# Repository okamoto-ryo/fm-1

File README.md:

# fm-1
DIY FM synthesizer

## Overview
<a href="https://okamoto-ryo.github.io/fm-1.html" target="_blank">FM-1</a>

## Requirements
- ARM KEIL uVision 5.0

## やること
- サイン波をsvfで生成するようにする
- ディスプレイのグラフィックを改善
- エンベロープのasymp化
- パラメーター追加
  - LFOの種類

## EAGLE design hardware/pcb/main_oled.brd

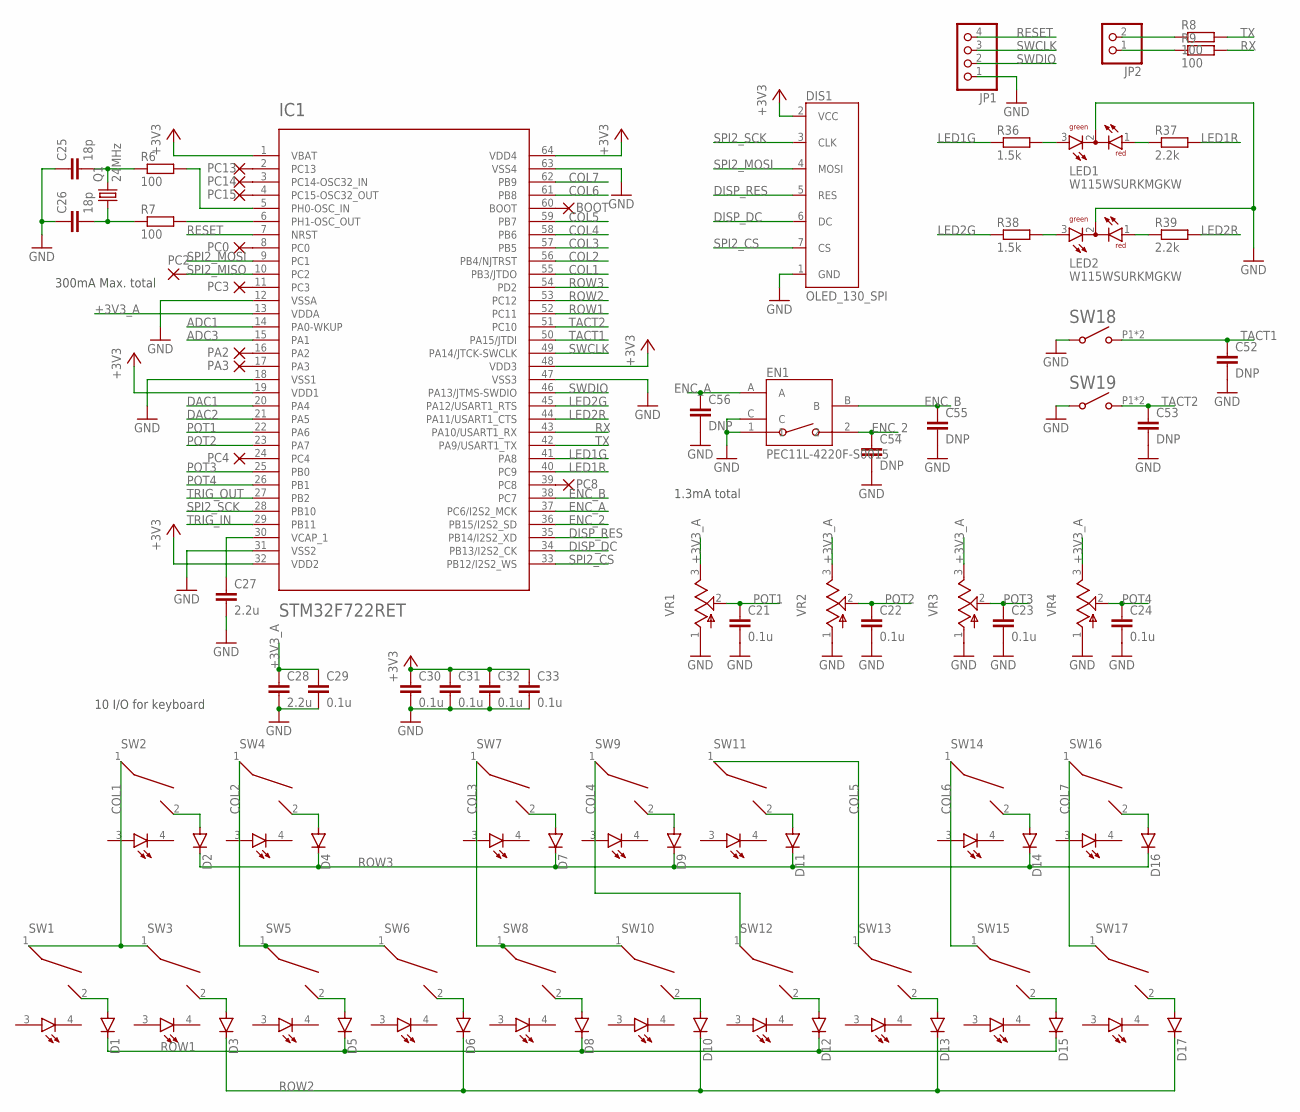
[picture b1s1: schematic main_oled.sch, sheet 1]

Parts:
BOOT: WIREPAD1,6/0,9; 1,6/0,9
C21, C22, C23, C24, C29, C30, C31, C32, C33: 0.1u; C0603
C25, C26: 18p; C0603
C27, C28: 2.2u; C0805
C52, C53, C54, C55, C56: DNP; C0603
D1, D2, D3, D4, D5, D6, D7, D8, D9, D10, D11, D12, D13, D14, D15, D16, D17: DIODE-SOD123; SOD123
DIS1: OLED_130_SPI
EN1: PEC11L-4220F-S0015
IC1: STM32F722RET; TQFP64
JP1: PINHD-1X4; 1X04
JP2: PINHD-1X2; 1X02
LED1, LED2: W115WSURKMGKW
PA2, PA3: WIREPAD1,6/0,9; 1,6/0,9
PC0, PC2, PC3, PC4, PC8, PC13, PC14, PC15: WIREPAD1,6/0,9; 1,6/0,9
Q1: 24MHz; HC49UP
R6, R7, R8, R9: 100; R0603
R36, R38: 1.5k; R0603
R37, R39: 2.2k; R0603
SW1, SW2, SW3, SW4, SW5, SW6, SW7, SW8, SW9, SW10, SW11, SW12, SW13, SW14, SW15, SW16, SW17: CHERRY_MX_LED_WITH_FIXING_PINS; MX1A-XX[R/G/Y]W
SW18, SW19: TACT_TH
VR1, VR2, VR3, VR4: 9MM_V

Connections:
+3V3: C30.1, C31.1, C32.1, C33.1, DIS1.2 (VCC), IC1.1 (VBAT), IC1.19 (VDD1), IC1.32 (VDD2), IC1.48 (VDD3), IC1.64 (VDD4); also elsewhere on the board
+3V3_A: C28.1, C29.1, IC1.13 (VDDA), VR1.3, VR2.3, VR3.3, VR4.3; also elsewhere on the board
ADC1: IC1.14 (PA0-WKUP); also elsewhere on the board
ADC3: IC1.15 (PA1); also elsewhere on the board
COL1: IC1.55 (PB3/JTDO), SW1.1, SW2.1, SW3.1
COL2: IC1.56 (PB4/NJTRST), SW4.1, SW5.1, SW6.1
COL3: IC1.57 (PB5), SW7.1, SW8.1, SW10.1
COL4: IC1.58 (PB6), SW9.1, SW12.1
COL5: IC1.59 (PB7), SW11.1, SW13.1
COL6: IC1.61 (PB8), SW14.1, SW15.1
COL7: IC1.62 (PB9), SW16.1, SW17.1
DAC1: IC1.20 (PA4); also elsewhere on the board
DAC2: IC1.21 (PA5); also elsewhere on the board
DISP_DC: DIS1.6 (DC), IC1.34 (PB13/I2S2_CK)
DISP_RES: DIS1.5 (RES), IC1.35 (PB14/I2S2_XD)
ENC_2: C54.1, EN1.2, IC1.36 (PB15/I2S2_SD)
ENC_A: C56.1, EN1.A, IC1.37 (PC6/I2S2_MCK)
ENC_B: C55.1, EN1.B, IC1.38 (PC7)
GND: C21.2, C22.2, C23.2, C24.2, C25.1, C26.1, C27.2, C28.2, C29.2, C30.2, C31.2, C32.2, C33.2, C52.2, C53.2, C54.2, C55.2, C56.2, DIS1.1 (GND), EN1.1, EN1.C, IC1.12 (VSSA), IC1.18 (VSS1), IC1.31 (VSS2), IC1.47 (VSS3), IC1.63 (VSS4), JP1.1, LED1.2 (C), LED2.2 (C), SW18.P3 (2), SW18.P4 (2), SW19.P3 (2), SW19.P4 (2), VR1.1, VR2.1, VR3.1, VR4.1; also elsewhere on the board
LED1G: IC1.41 (PA8), R36.1
LED1R: IC1.40 (PC9), R37.2
LED2G: IC1.45 (PA12/USART1_RTS), R38.1
LED2R: IC1.44 (PA11/USART1_CTS), R39.2
unnamed: LED1.3 (AG), R36.2
unnamed: LED1.1 (AR), R37.1
unnamed: LED2.3 (AG), R38.2
unnamed: LED2.1 (AR), R39.1
unnamed: IC1.2 (PC13), PC13.1
unnamed: IC1.3 (PC14-OSC32_IN), PC14.1
unnamed: IC1.4 (PC15-OSC32_OUT), PC15.1
unnamed: IC1.8 (PC0), PC0.1
unnamed: IC1.11 (PC3), PC3.1
unnamed: D1.A, SW1.2
unnamed: D2.A, SW2.2
unnamed: D3.A, SW3.2
unnamed: D4.A, SW4.2
unnamed: D5.A, SW5.2
unnamed: D6.A, SW6.2
unnamed: D7.A, SW7.2
unnamed: D8.A, SW8.2
unnamed: D9.A, SW9.2
unnamed: D10.A, SW10.2
unnamed: D11.A, SW11.2
unnamed: D12.A, SW12.2
unnamed: D13.A, SW13.2
unnamed: D14.A, SW14.2
unnamed: D15.A, SW15.2
unnamed: D16.A, SW16.2
unnamed: D17.A, SW17.2
unnamed: IC1.16 (PA2), PA2.1
unnamed: JP2.1, R9.1
unnamed: JP2.2, R8.1
unnamed: IC1.5 (PH0-OSC_IN), R6.2
unnamed: IC1.6 (PH1-OSC_OUT), R7.2
unnamed: C25.2, Q1.2, R6.1
unnamed: C26.2, Q1.1, R7.1
unnamed: C27.1, IC1.30 (VCAP_1)
unnamed: IC1.17 (PA3), PA3.1
unnamed: IC1.24 (PC4), PC4.1
unnamed: IC1.39 (PC8), PC8.1
unnamed: BOOT.1, IC1.60 (BOOT)
POT1: C21.1, IC1.22 (PA6), VR1.2
POT2: C22.1, IC1.23 (PA7), VR2.2
POT3: C23.1, IC1.25 (PB0), VR3.2
POT4: C24.1, IC1.26 (PB1), VR4.2
RESET: IC1.7 (NRST), JP1.4
ROW1: D1.C, D5.C, D8.C, D12.C, D15.C, IC1.52 (PC11)
ROW2: D3.C, D6.C, D10.C, D13.C, D17.C, IC1.53 (PC12)
ROW3: D2.C, D4.C, D7.C, D9.C, D11.C, D14.C, D16.C, IC1.54 (PD2)
RX: IC1.43 (PA10/USART1_RX), R9.2
SPI2_CS: DIS1.7 (CS), IC1.33 (PB12/I2S2_WS)
SPI2_MISO: IC1.10 (PC2), PC2.1
SPI2_MOSI: DIS1.4 (MOSI), IC1.9 (PC1)
SPI2_SCK: DIS1.3 (CLK), IC1.28 (PB10)
SWCLK: IC1.49 (PA14/JTCK-SWCLK), JP1.3
SWDIO: IC1.46 (PA13/JTMS-SWDIO), JP1.2
TACT1: C52.1, IC1.50 (PA15/JTDI), SW18.P1 (1), SW18.P2 (1)
TACT2: C53.1, IC1.51 (PC10), SW19.P1 (1), SW19.P2 (1)
TRIG_IN: IC1.29 (PB11); also elsewhere on the board
TRIG_OUT: IC1.27 (PB2); also elsewhere on the board
TX: IC1.42 (PA9/USART1_TX), R8.2

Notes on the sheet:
10 I/O for keyboard
300mA Max. total
1.3mA total

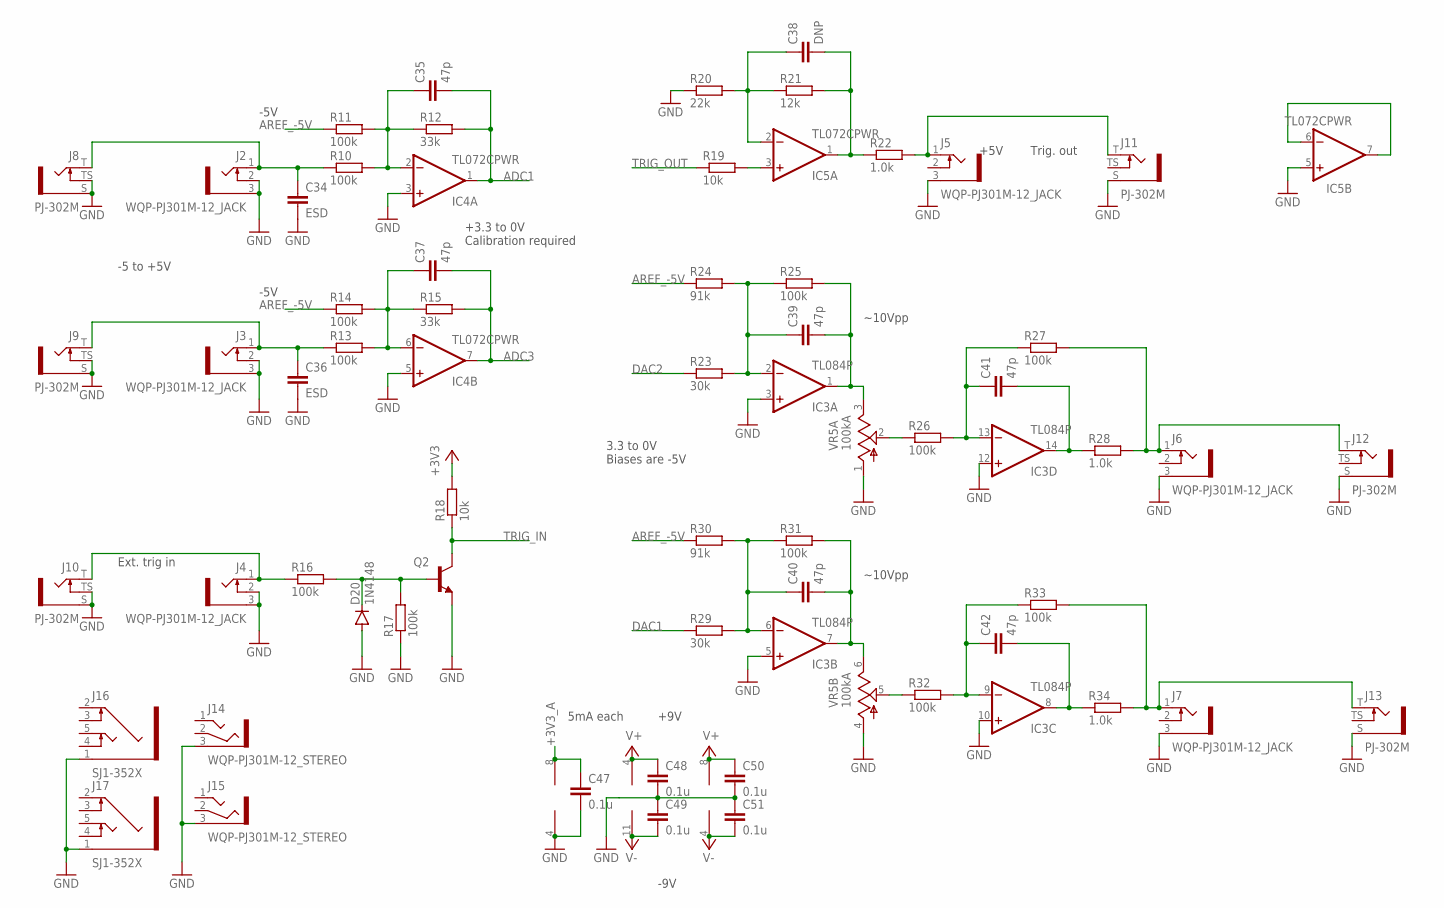
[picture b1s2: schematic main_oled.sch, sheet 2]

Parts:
C34, C36: ESD; C0603
C35, C37, C39, C40, C41, C42: 47p; C0603
C38: DNP; C0603
C47, C48, C49, C50, C51: 0.1u; C0603
D20: 1N4148; SOD123
IC3: TL084P; TSSOP14
IC4, IC5: TL072CPWR; TSSOP8
J2, J3, J4, J5, J6, J7: WQP-PJ301M-12_JACK
J8, J9, J10, J11, J12, J13: PJ-302M
J14, J15: WQP-PJ301M-12_STEREO; WQP-PJ301M-12_JACK
J16, J17: SJ1-352X
Q2: MMBT3904LT1-NPN-SOT23-BEC; SOT23-BEC
R10, R11, R13, R14, R16, R17, R25, R26, R27, R31, R32, R33: 100k; R0603
R12, R15: 33k; R0603
R18, R19: 10k; R0603
R20: 22k; R0603
R21: 12k; R0603
R22, R28, R34: 1.0k; R0603
R23, R29: 30k; R0603
R24, R30: 91k; R0603
VR5: 100kA; 9MM_V_DUAL

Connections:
+3V3: R18.2; also elsewhere on the board
+3V3_A: C47.1, IC4.8 (V+); also elsewhere on the board
ADC1: C35.2, IC4.1 (OUT), R12.2; also elsewhere on the board
ADC3: C37.2, IC4.7 (OUT), R15.2; also elsewhere on the board
AREF_-5V: R11.1, R14.1, R24.1, R30.1; also elsewhere on the board
DAC1: R29.1; also elsewhere on the board
DAC2: R23.1; also elsewhere on the board
GND: C34.2, C36.2, C47.2, C48.2, C49.1, C50.2, C51.1, D20.A, IC3.3 (+IN), IC3.5 (+IN), IC3.10 (+IN), IC3.12 (+IN), IC4.3 (+IN), IC4.4 (V-), IC4.5 (+IN), IC5.5 (+IN), J2.2 (3), J2.3 (1), J3.2 (3), J3.3 (1), J4.2 (3), J4.3 (1), J5.3 (1), J6.3 (1), J7.3 (1), J8.S (1), J8.TS (3), J9.S (1), J9.TS (3), J10.S (1), J10.TS (3), J11.S (1), J12.S (1), J13.S (1), J14.3 (1), J15.3 (1), J16.1 (S), J17.1 (S), Q2.E, R17.1, R20.1, VR5.1, VR5.4 (1); also elsewhere on the board
unnamed: C34.1, J2.1 (2), J8.T (2), R10.1
unnamed: C35.1, IC4.2 (-IN), R10.2, R11.2, R12.1
unnamed: J4.1 (2), J10.T (2), R16.1
unnamed: C36.1, J3.1 (2), J9.T (2), R13.1
unnamed: C37.1, IC4.6 (-IN), R13.2, R14.2, R15.1
unnamed: D20.C, Q2.B, R16.2, R17.2
unnamed: R26.1, VR5.2
unnamed: C39.1, IC3.2 (-IN), R23.2, R24.2, R25.1
unnamed: J6.1 (2), J12.T (2), R27.2, R28.2
unnamed: C41.1, IC3.13 (-IN), R26.2, R27.1
unnamed: C40.1, IC3.6 (-IN), R29.2, R30.2, R31.1
unnamed: C41.2, IC3.14 (OUT), R28.1
unnamed: R32.1, VR5.5 (2)
unnamed: C38.2, IC5.1 (OUT), R21.2, R22.1
unnamed: C39.2, IC3.1 (OUT), R25.2, VR5.3
unnamed: C40.2, IC3.7 (OUT), R31.2, VR5.6 (3)
unnamed: C42.1, IC3.9 (-IN), R32.2, R33.1
unnamed: C42.2, IC3.8 (OUT), R34.1
unnamed: J7.1 (2), J13.T (2), R33.2, R34.2
unnamed: C38.1, IC5.2 (-IN), R20.2, R21.1
unnamed: IC5.3 (+IN), R19.2
unnamed: J5.1 (2), J11.T (2), R22.2
unnamed: IC5.6 (-IN), IC5.7 (OUT)
TRIG_IN: Q2.C, R18.1; also elsewhere on the board
TRIG_OUT: R19.1; also elsewhere on the board
V+: C48.1, C50.1, IC3.4 (V+), IC5.8 (V+); also elsewhere on the board
V-: C49.2, C51.2, IC3.11 (V-), IC5.4 (V-); also elsewhere on the board

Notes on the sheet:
5mA each
Ext. trig in
Trig. out
3.3 to 0V Biases are -5V
+5V
-5 to +5V
+3.3 to 0V Calibration required
-5V
~10Vpp
-9V
+9V

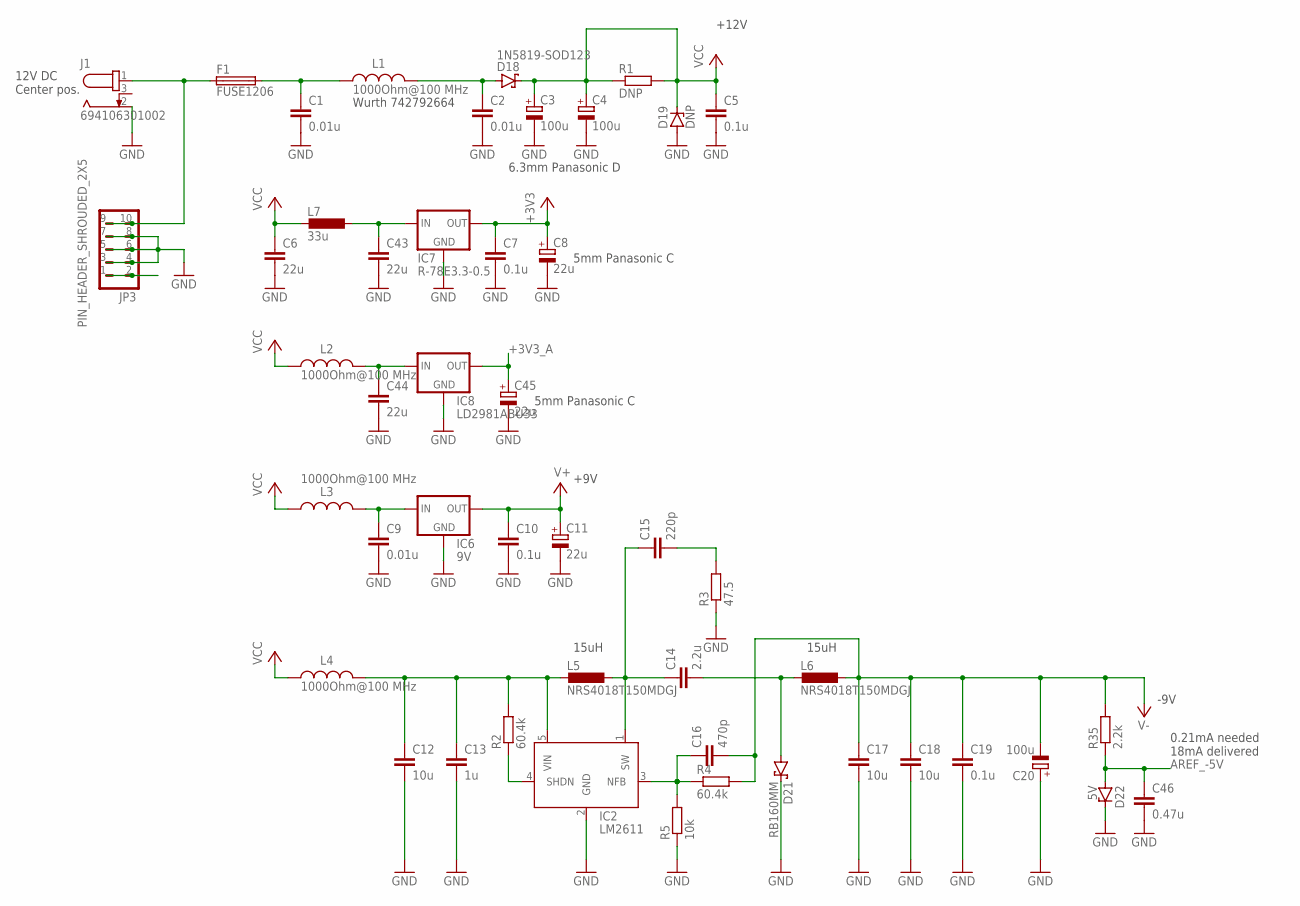
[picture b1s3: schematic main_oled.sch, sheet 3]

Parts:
C1, C2, C9: 0.01u; C0603
C3, C4, C20: 100u; PANASONIC_D
C5, C7, C10, C19: 0.1u; C0603
C6, C43, C44: 22u; C1206
C8, C11, C45: 22u; PANASONIC_C
C12, C17, C18: 10u; C0805
C13: 1u; C0805
C14: 2.2u; C0805
C15: 220p; C0603
C16: 470p; C0603
C46: 0.47u; C0603
D18: 1N5819-SOD123; SOD123
D19: DNP; SOT23
D21: RB160MM; SOD123
D22: 5V; SOD123
F1: FUSE1206; R1206
IC2: LM2611; SOT23-5
IC6: 9V; TO252-3
IC7: R-78E3.3-0.5; R-78E
IC8: LD2981ABU33; SOT89R
J1: 694106301002
JP3: PIN_HEADER_SHROUDED_2X5
L1, L2, L3, L4: 1000Ohm@100 MHz; WE-CBF_0603(W=2.2)
L5, L6: NRS4018T150MDGJ; NR40XX
L7: 33u; L2012C
R1: DNP; R1210
R2, R4: 60.4k; R0603
R3: 47.5; R0603
R5: 10k; R0603
R35: 2.2k; R0603

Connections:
+3V3: C7.1, C8.+, IC7.3 (OUT); also elsewhere on the board
+3V3_A: C45.+, IC8.2 (OUT); also elsewhere on the board
AREF_-5V: C46.1, D22.A, R35.1; also elsewhere on the board
GND: C1.2, C2.2, C3.-, C4.-, C5.2, C6.2, C7.2, C8.-, C9.2, C10.2, C11.-, C12.2, C13.2, C17.2, C18.2, C19.2, C20.+, C43.2, C44.2, C45.-, C46.2, D19.1 (A), D21.C, D22.C, IC2.2 (GND), IC6.GND, IC7.2 (GND), IC8.3 (GND), IC8.4 (GND), J1.2, JP3.3, JP3.4, JP3.5, JP3.6, JP3.7, JP3.8, R3.1, R5.1; also elsewhere on the board
unnamed: F1.1, J1.1, JP3.9, JP3.10
unnamed: C2.1, D18.A, L1.2
unnamed: C1.1, F1.2, L1.1
unnamed: C12.1, C13.1, IC2.5 (VIN), L4.2, L5.2, R2.2
unnamed: C14.1, C15.1, IC2.1 (SW), L5.1
unnamed: IC2.4 (SHDN), R2.1
unnamed: C15.2, R3.2
unnamed: C16.1, IC2.3 (NFB), R4.1, R5.2
unnamed: C14.2, D21.A, L6.2
unnamed: C9.1, IC6.IN, L3.2
unnamed: C43.1, IC7.1 (IN), L7.1
unnamed: C44.1, IC8.1 (IN), L2.2
unnamed: JP3.1, JP3.2
V+: C10.1, C11.+, IC6.OUT; also elsewhere on the board
V-: C16.2, C17.1, C18.1, C19.1, C20.-, L6.1, R4.2, R35.2; also elsewhere on the board
VCC: C3.+, C4.+, C5.1, C6.1, D18.C, D19.3 (C), L2.1, L3.1, L4.1, L7.2, R1.1, R1.2

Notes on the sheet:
12V DC Center pos.
Wurth 742792664
6.3mm Panasonic D
+12V
-9V
15uH
+9V
5mm Panasonic C
0.21mA needed 18mA delivered

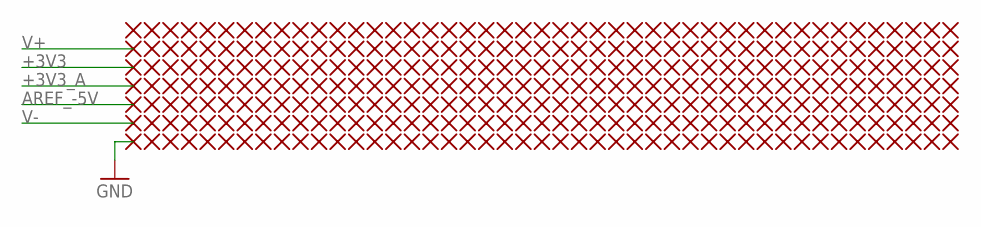
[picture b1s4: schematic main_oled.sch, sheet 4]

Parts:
P1, P2, P3, P4, P5, P6, P7, P8, P9, P10, P11, P12, P13, P14, P15, P16, P17, P18, P19, P20, P21, P22, P23, P24, P25, P26, P27, P28, P29, P30, P31, P32, P33, P34, P35, P36, P37, P38, P39, P40, P41, P42, P43, P44, P45, P46, P47, P48, P49, P50, P51, P52, P53, P54, P55, P56, P57, P58, P59, P60, P61, P62, P63, P64, P65, P66, P67, P68, P69, P70, P71, P72, P73, P74, P75, P76, P77, P78, P79, P80, P81, P82, P83, P84, P85, P86, P87, P88, P89, P90, P91, P92, P93, P94, P95, P96, P97, P98, P99, P100, P101, P102, P103, P104, P105, P106, P107, P108, P109, P110, P111, P112, P113, P114, P115, P116, P117, P118, P119, P120, P121, P122, P123, P124, P125, P126, P127, P128, P129, P130, P131, P132, P133, P134, P135, P136, P137, P138, P139, P140, P141, P142, P143, P144, P145, P146, P147, P148, P149, P150, P151, P152, P153, P154, P155, P156, P157, P158, P159, P160, P161, P162, P163, P164, P165, P166, P167, P168, P169, P170, P171, P172, P173, P174, P175, P176, P177, P178, P179, P180, P181, P182, P183, P184, P185, P186, P187, P188, P189, P190, P191, P192, P193, P194, P195, P196, P197, P198, P199, P200, P201, P202, P203, P204, P205, P206, P207, P208, P209, P210, P211, P212, P213, P214, P215, P216, P217, P218, P219, P220, P221, P222, P223, P224, P225, P226, P227, P228, P229, P230, P231, P232, P233, P234, P235, P236, P237, P238, P239, P240, P241, P242, P243, P244, P245, P246, P247, P248, P249, P250, P251, P252, P253, P254, P255, P256, P257, P258, P259, P260, P261, P262, P263, P264, P265, P266, P267, P268, P269, P270, P271, P272, P273, P274, P275, P276, P277, P278, P279, P280, P281, P282, P283, P284, P285, P286, P287, P288, P289, P290, P291, P292, P293, P294, P295, P296, P297, P298, P299, P300, P301, P302, P303, P304, P305, P306, P307, P308, P309, P310, P311, P312, P313, P314, P315: PERF_2.54

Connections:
+3V3: P3.1; also elsewhere on the board
+3V3_A: P4.1; also elsewhere on the board
AREF_-5V: P5.1; also elsewhere on the board
GND: P7.1; also elsewhere on the board
V+: P2.1; also elsewhere on the board
V-: P6.1; also elsewhere on the board

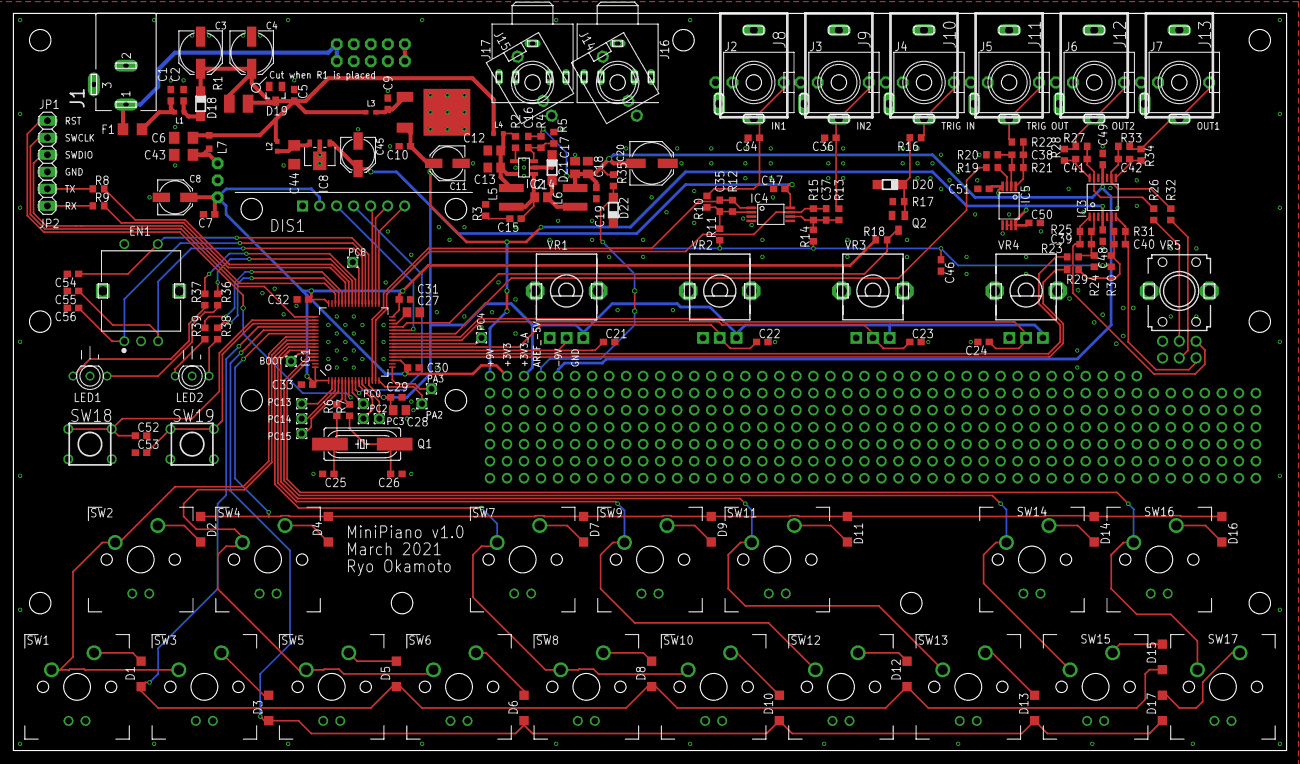
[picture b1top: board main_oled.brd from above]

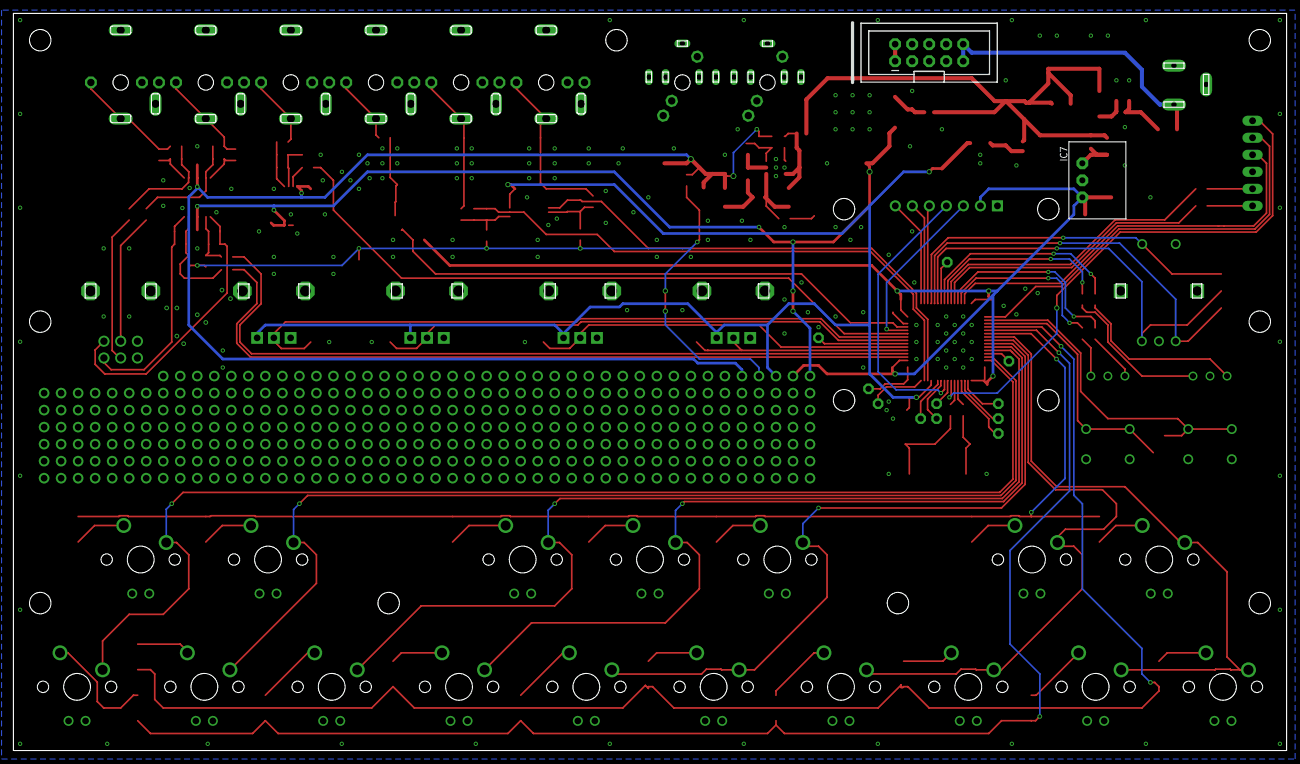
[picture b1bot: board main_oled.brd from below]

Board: 2 copper layers, 190.0 x 110.0 mm, 509 parts (2 on the bottom side), 121 nets.

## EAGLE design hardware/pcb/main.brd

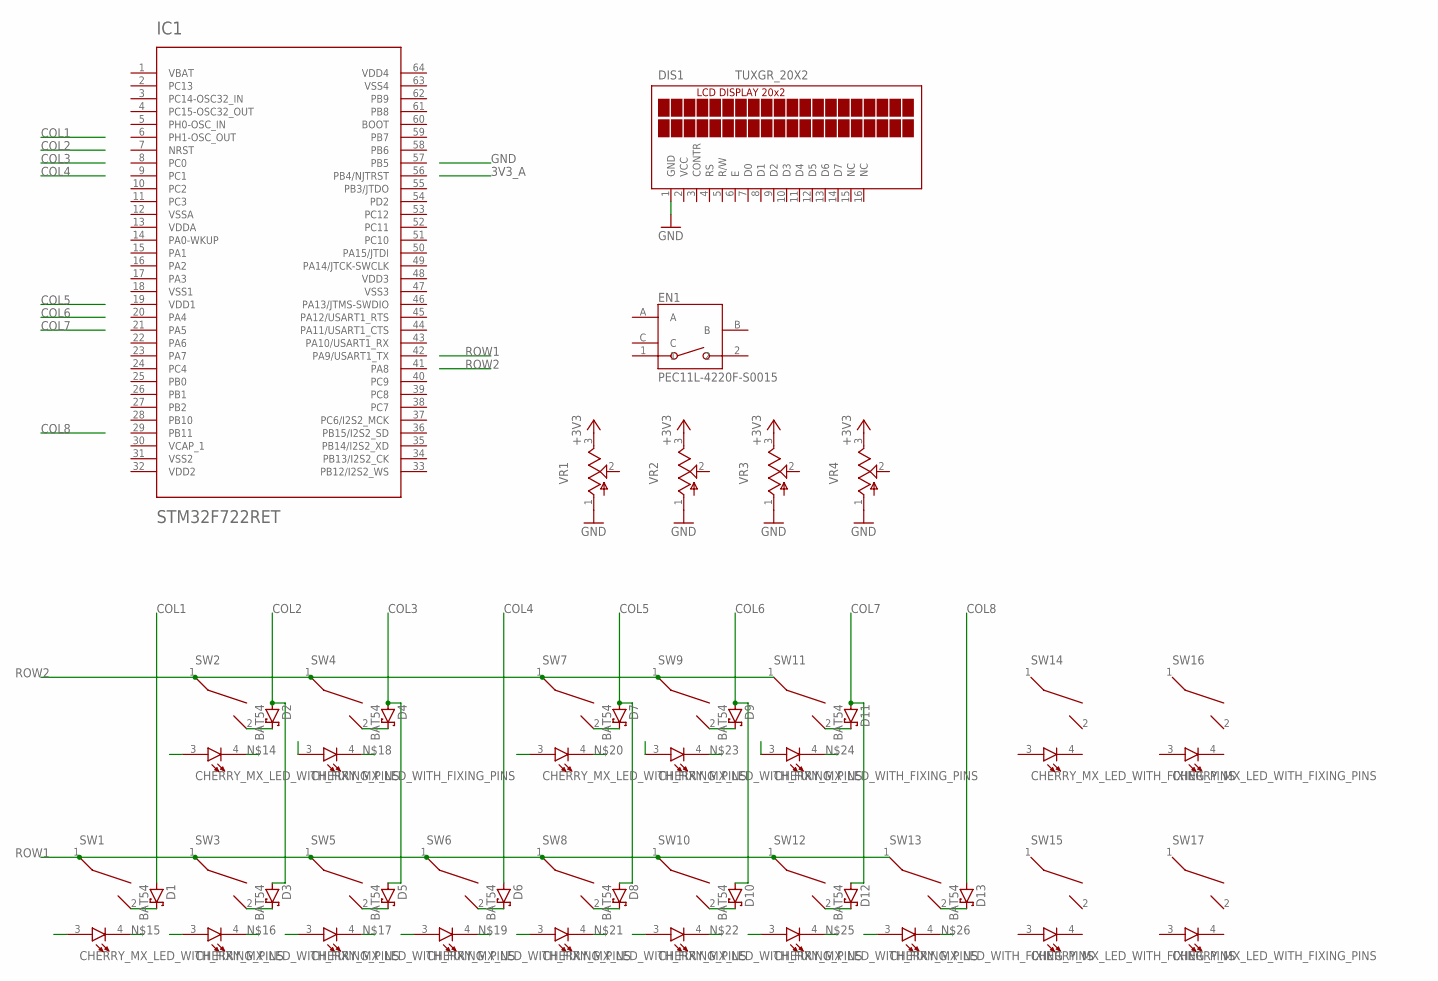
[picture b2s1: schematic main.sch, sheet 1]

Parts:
D1, D2, D3, D4, D5, D6, D7, D8, D9, D10, D11, D12, D13: BAT54; SOT23
DIS1: TUXGR_20X2
EN1: PEC11L-4220F-S0015
IC1: STM32F722RET; TQFP64
SW1, SW2, SW3, SW4, SW5, SW6, SW7, SW8, SW9, SW10, SW11, SW12, SW13, SW14, SW15, SW16, SW17: CHERRY_MX_LED_WITH_FIXING_PINS; MX1A-XX[R/G/Y]W
VR1, VR2, VR3, VR4: 9MM_V

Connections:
+3V3: VR1.3, VR2.3, VR3.3, VR4.3; also elsewhere on the board
COL1: D1.1 (A)
COL2: D2.1 (A), D3.1 (A)
COL3: D4.1 (A), D5.1 (A)
COL4: D6.1 (A)
COL5: D7.1 (A), D8.1 (A)
COL6: D9.1 (A), D10.1 (A)
COL7: D11.1 (A), D12.1 (A)
COL8: D13.1 (A)
GND: DIS1.1 (GND), VR1.1, VR2.1, VR3.1, VR4.1; also elsewhere on the board
unnamed: D2.3 (C), SW2.2
unnamed: D4.3 (C), SW4.2
unnamed: D7.3 (C), SW7.2
unnamed: D9.3 (C), SW9.2
unnamed: D11.3 (C), SW11.2
unnamed: D1.3 (C), SW1.2
unnamed: D3.3 (C), SW3.2
unnamed: D5.3 (C), SW5.2
unnamed: D6.3 (C), SW6.2
unnamed: D8.3 (C), SW8.2
unnamed: D10.3 (C), SW10.2
unnamed: D12.3 (C), SW12.2
unnamed: D13.3 (C), SW13.2
ROW1: SW1.1, SW3.1, SW5.1, SW6.1, SW8.1, SW10.1, SW12.1, SW13.1
ROW2: SW2.1, SW4.1, SW7.1, SW9.1, SW11.1
VCC: DIS1.2 (VCC); also elsewhere on the board

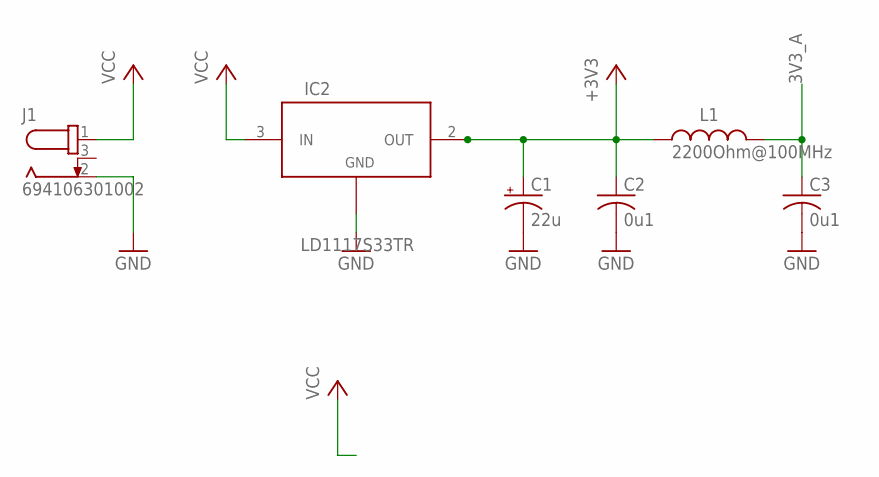
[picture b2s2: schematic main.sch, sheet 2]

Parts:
C1: 22u; PANASONIC_C
C2, C3: 0u1; C0603
IC2: LD1117S33TR; SOT-223
J1: 694106301002
L1: 2200Ohm@100MHz; WE-CBF_0603(W=2.2)

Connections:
3V3_A: C3.1, L1.2
+3V3: C1.+, C2.1, IC2.2 (OUT), IC2.4, L1.1; also elsewhere on the board
GND: C1.-, C2.2, C3.2, IC2.1 (ADJ/GND), J1.2; also elsewhere on the board
VCC: IC2.3 (IN), J1.1; also elsewhere on the board

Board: 2 copper layers, 43 parts (0 on the bottom side), 24 nets, no tracks yet.

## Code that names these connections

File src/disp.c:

#include "disp.h"
#include "stm32f722xx.h"
#include "timer.h"
#include <stdio.h>
#include <string.h>

#define CMD_BUF_LEN 32

uint8_t dispBuf[1056];
uint8_t curDispPage = 0;
uint8_t dmaHandlerState = 0;

extern const uint8_t font1[128][6];

void DispInit(void) {		// Interrupts are not enabled yet
	RCC->AHB1ENR |= RCC_AHB1ENR_GPIOBEN
								| RCC_AHB1ENR_GPIOCEN;
	GPIOB->MODER &= ~(GPIO_MODER_MODER10_Msk | GPIO_MODER_MODER12_Msk | 
										GPIO_MODER_MODER13_Msk | GPIO_MODER_MODER14_Msk);
	GPIOB->MODER |= 2U << GPIO_MODER_MODER10_Pos | 2U << GPIO_MODER_MODER12_Pos | 
									1U << GPIO_MODER_MODER13_Pos | 1U << GPIO_MODER_MODER14_Pos;
	GPIOB->AFR[1] |= 5U << GPIO_AFRH_AFRH2_Pos | 5U << GPIO_AFRH_AFRH4_Pos;		// PB10 is SPI2_SCK and PB12 is SPI2_NSS
	GPIOC->MODER &= ~GPIO_MODER_MODER1_Msk;
	GPIOC->MODER |= 2U << GPIO_MODER_MODER1_Pos;
	GPIOC->AFR[0] |= 5U << GPIO_AFRL_AFRL1_Pos;		// PC1 is SPI2_MOSI
	
	RCC->APB1ENR |= RCC_APB1ENR_SPI2EN;
	SPI2->CR1 |= 5U << SPI_CR1_BR_Pos		// Baud rate is fPCLK / 128
						 | SPI_CR1_MSTR
						 | SPI_CR1_CPOL
						 | SPI_CR1_CPHA;
	SPI2->CR2 |= 15U << SPI_CR2_DS_Pos
						 | SPI_CR2_SSOE						// NSS output enable
						 | SPI_CR2_TXDMAEN;
	
	RCC->AHB1ENR |= RCC_AHB1ENR_DMA1EN;
	DMA1_Stream4->CR |= 0U << DMA_SxCR_CHSEL_Pos
										| 1U << DMA_SxCR_MSIZE_Pos
										| 1U << DMA_SxCR_PSIZE_Pos
										| DMA_SxCR_MINC
										| 1U << DMA_SxCR_DIR_Pos
										| DMA_SxCR_TCIE;
	DMA1_Stream4->NDTR = 66;
	DMA1_Stream4->PAR = (uint32_t)&(SPI2->DR);
	DMA1_Stream4->M0AR = (uint32_t)&dispBuf;
	
	// GPIOB->BSRR |= GPIO_BSRR_BS12;		// CS high	// Done with SPI2 NSS
	GPIOB->BSRR |= GPIO_BSRR_BR14;		// Pull the reset pin low
	Delay(100);
	GPIOB->BSRR |= GPIO_BSRR_BS14;		// Pull the reset pin high
	GPIOB->BSRR |= GPIO_BSRR_BR13;		// A0 (CD) low = command
	// GPIOB->BSRR |= GPIO_BSRR_BR12;		// CS low
	SPI2->CR1 |= SPI_CR1_SPE;
	SPI2->DR = 0x0210;
	Delay(10000);
	SPI2->DR = 0xAFAF;
	Delay(10000);
	GPIOB->BSRR |= GPIO_BSRR_BS13;		// A0 is read at 8th clock rise so don't toggle too early
	// can send data now
	
//	for (uint8_t i = 0; i < 132; i++) {
//		for (uint8_t j = 0; j < 8; j++) {
//			dispBuf[j * 132 + i] = ((i >> j) & 1U) ? 0xFF : 0U;
//			dispBuf[j * 132 + i] = 0xFF;
//			dispBuf[j * 132 + i] = (i == 0 || i == 127) ? 0xFF : 0U;
//		}
//	}
}

void DispOn(void) {
	// Send Display on command to the display
	StartDispDMA();
}

void StartDispDMA(void) {
	GPIOB->BSRR |= GPIO_BSRR_BS13;
	DMA1->HIFCR |= DMA_HIFCR_CTCIF4
							 | DMA_HIFCR_CHTIF4;
	DMA1_Stream4->CR |= DMA_SxCR_EN;
}

void DMA1_Stream4_IRQHandler(void);
void DMA1_Stream4_IRQHandler(void) {
	DMA1_Stream4->CR &= ~DMA_SxCR_EN;
	dmaHandlerState = 0;
	TIM7->CNT = 0;
	TIM7->ARR = 2000;
	TIM7->CR1 |= TIM_CR1_CEN;
	
	DMA1->HIFCR |= DMA_HIFCR_CTCIF4
							 | DMA_HIFCR_CHTIF4;
}

void TIM7_IRQHandler(void);
void TIM7_IRQHandler(void) {
	TIM7->CR1 &= ~TIM_CR1_CEN;
	
	switch (dmaHandlerState) {
		case 0:
			GPIOB->BSRR |= GPIO_BSRR_BR13;
			curDispPage++;
			if (curDispPage > 7) {
				curDispPage = 0;
			}
			SPI2->DR = 0x0210;
			
			TIM7->CNT = 0;
			TIM7->ARR = 2000;
			TIM7->CR1 |= TIM_CR1_CEN;
			dmaHandlerState = 1;
			break;
		case 1:
			SPI2->DR = 0x10B0 | curDispPage;
			
			TIM7->CNT = 0;
			TIM7->ARR = 2000;
			TIM7->CR1 |= TIM_CR1_CEN;
			dmaHandlerState = 2;
			break;
		case 2:
			DMA1_Stream4->M0AR = (uint32_t)&dispBuf + 132 * curDispPage;
			StartDispDMA();
			dmaHandlerState = 0;
			break;
		default:
			dmaHandlerState = 0;
			break;
	}
	
	TIM7->SR &= ~TIM_SR_UIF_Msk;
}

void SetPixel(uint8_t x, uint8_t y) {
	x = 127 - x; y = 63 - y;
	dispBuf[(x & 1U) ? ((y >> 3) * 132 + x - 1) : ((y >> 3) * 132 + x + 1)] |= 1U << (y % 8);
}

void ClearAll(void) {
	for (uint32_t i = 0; i < 1056; i++) {
		dispBuf[i] = 0U;
	}
}

void PutChar(uint8_t x, uint8_t y, char ltr) {
	if (ltr < 128 && x < 21 && y < 8) {
		uint8_t xPx = 1 + 6 * x;
		for (int i = 0; i < 6; i++) {
			dispBuf[((127 - xPx) & 1U) ? ((7 - y) * 132 + (127 - xPx) - 1) : ((7 - y) * 132 + (127 - xPx) + 1)] = font1[(uint8_t)ltr][i];
			xPx++;
		}
	}
}

void DrawString(uint8_t x, uint8_t y, char* str, uint8_t len) {
	for (int i = 0; i < len; i++) {
		PutChar((uint8_t)(x + i), y, str[i]);
	}
}

void DrawValue(uint8_t x, uint8_t y, const char* str, float val) {
	char buf[32];
	sprintf(buf, str, val);
	DrawString(x, y, buf, (uint8_t)strlen(buf));
}

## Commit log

2023-05-22 Added everything
2023-05-22 Update README.md
    Listed things to do
2023-05-22 Cleaned comments up
2023-06-15 Add case laser cutting data
2023-06-15 Add eagle files
2023-06-15 Sort files out

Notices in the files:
parts and their libraries:
Wurth_EMC Components_WE-CBF: Copyright: Würth Elektronik
